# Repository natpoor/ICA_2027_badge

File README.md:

Arduino code and KiCAD files for the (v 0.2) ICA 2027 conference badge in Glasgow, Scotland.
The code works on the v 0.1 board (which is not posted here), the main change is the silkscreen but it should all work.
Most of the button-press (debouncing) and the sleep functions were (re)written by Claude Code (fall 2027 version).

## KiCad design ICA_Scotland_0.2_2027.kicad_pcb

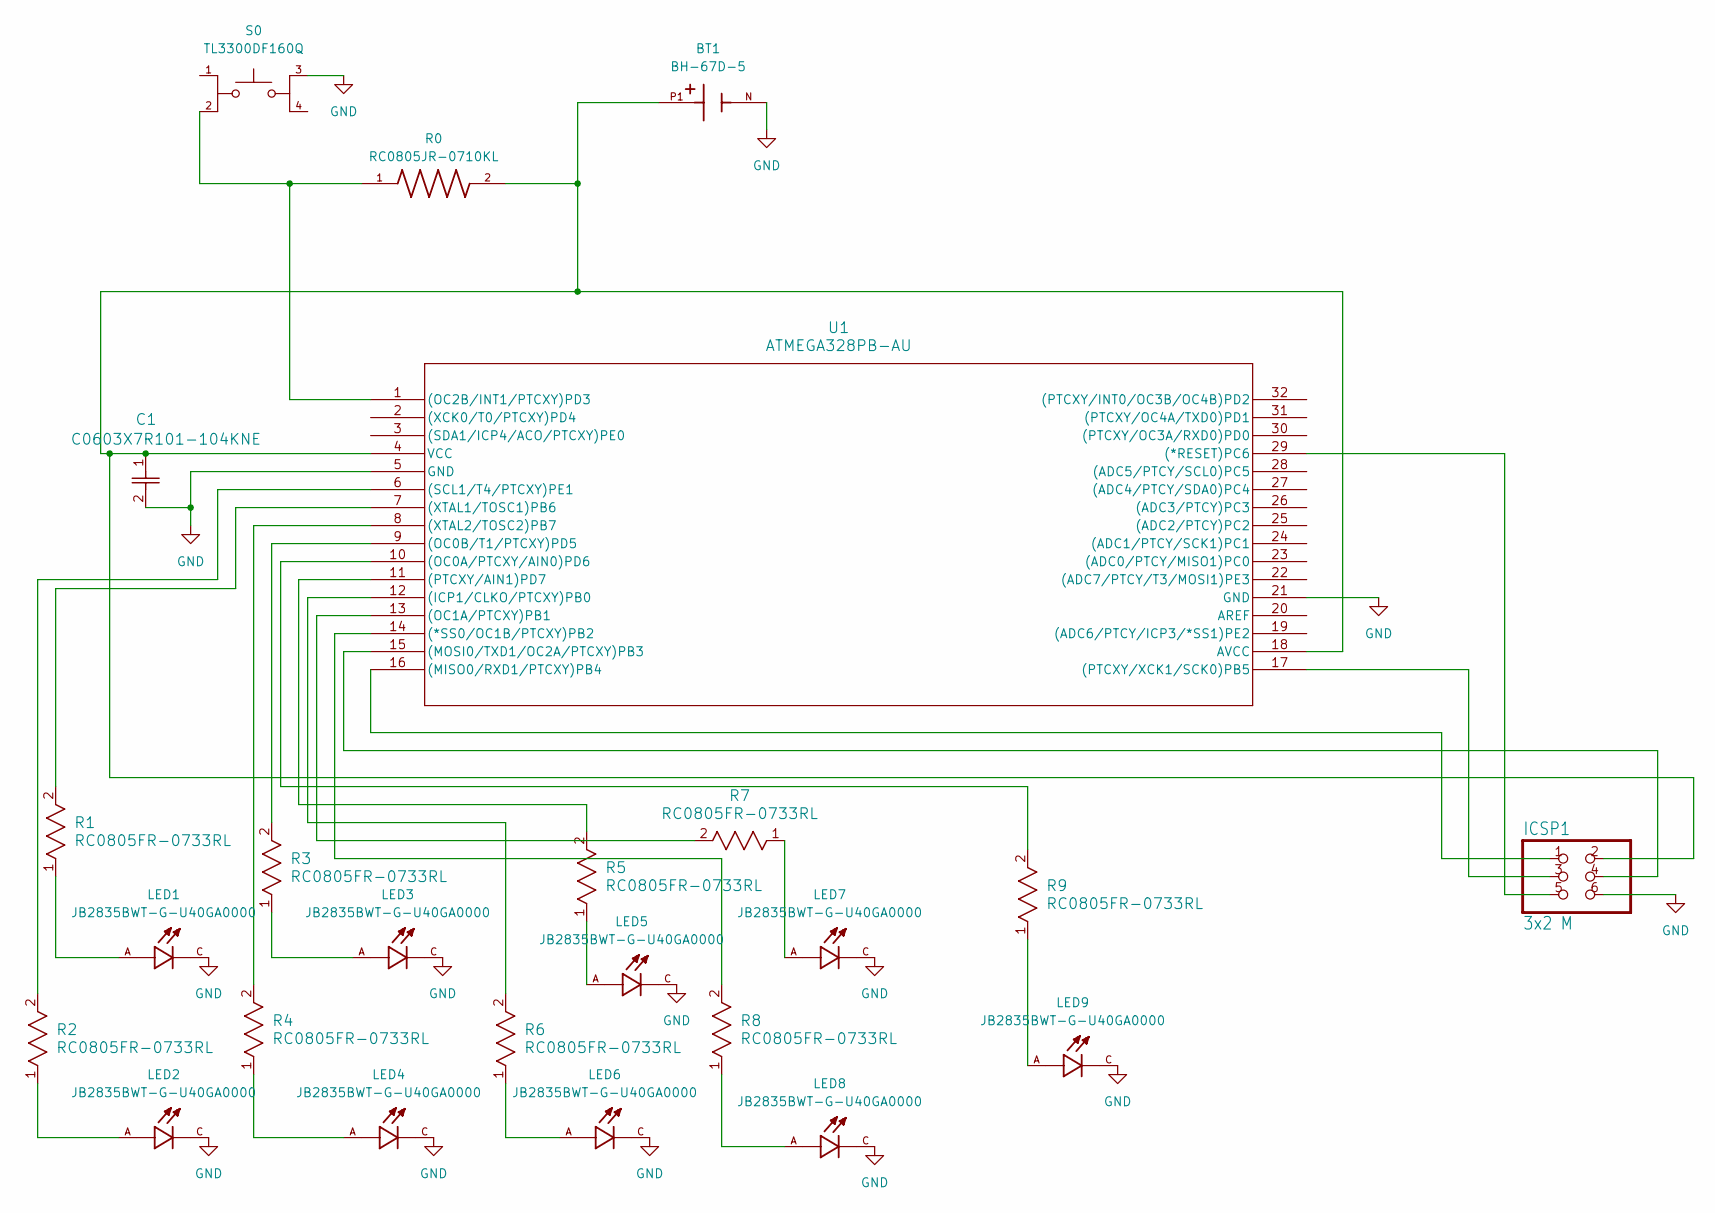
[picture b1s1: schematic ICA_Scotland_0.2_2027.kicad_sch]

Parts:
BT1: BH-67D-5; BAT_BH-67D-5; PARTREV A
C1: C0603X7R101-104KNE; CAP_C0603_VEN
ICSP1: 3x2 M; Conn_02x03_no_silk
LED1, LED2, LED3, LED4, LED5, LED6, LED7, LED8, LED9: JB2835BWT-G-U40GA0000; LED_JB2835BWT-G-U40GA0000-N0000001
R0: RC0805JR-0710KL; RESC2012X60N
R1, R2, R3, R4, R5, R6, R7, R8, R9: RC0805FR-0733RL; RC0805N_YAG
S0: TL3300DF160Q; SW_TL3300DF160Q; PARTREV A
U1: ATMEGA328PB-AU; 32A_MCH

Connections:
GND: BT1.N, C1.2, ICSP1.6, LED1.C, LED2.C, LED3.C, LED4.C, LED5.C, LED6.C, LED7.C, LED8.C, LED9.C, S0.3, U1.5 (GND), U1.21 (GND)
unnamed: LED1.A, R1.1
unnamed: LED2.A, R2.1
unnamed: LED3.A, R3.1
unnamed: LED4.A, R4.1
unnamed: LED5.A, R5.1
unnamed: LED6.A, R6.1
unnamed: LED7.A, R7.1
unnamed: LED8.A, R8.1
unnamed: LED9.A, R9.1
unnamed: ICSP1.5, U1.29 ((*RESET)PC6)
unnamed: R8.2, U1.14 ((*SS0/OC1B/PTCXY)PB2)
unnamed: R6.2, U1.12 ((ICP1/CLKO/PTCXY)PB0)
unnamed: ICSP1.1, U1.16 ((MISO0/RXD1/PTCXY)PB4)
unnamed: ICSP1.4, U1.15 ((MOSI0/TXD1/OC2A/PTCXY)PB3)
unnamed: R9.2, U1.10 ((OC0A/PTCXY/AIN0)PD6)
unnamed: R3.2, U1.9 ((OC0B/T1/PTCXY)PD5)
unnamed: R7.2, U1.13 ((OC1A/PTCXY)PB1)
unnamed: R0.1, S0.2, U1.1 ((OC2B/INT1/PTCXY)PD3)
unnamed: R5.2, U1.11 ((PTCXY/AIN1)PD7)
unnamed: ICSP1.3, U1.17 ((PTCXY/XCK1/SCK0)PB5)
unnamed: R2.2, U1.6 ((SCL1/T4/PTCXY)PE1)
unnamed: R1.2, U1.7 ((XTAL1/TOSC1)PB6)
unnamed: R4.2, U1.8 ((XTAL2/TOSC2)PB7)
unnamed: BT1.P1, C1.1, ICSP1.2, R0.2, U1.4 (VCC), U1.18 (AVCC)

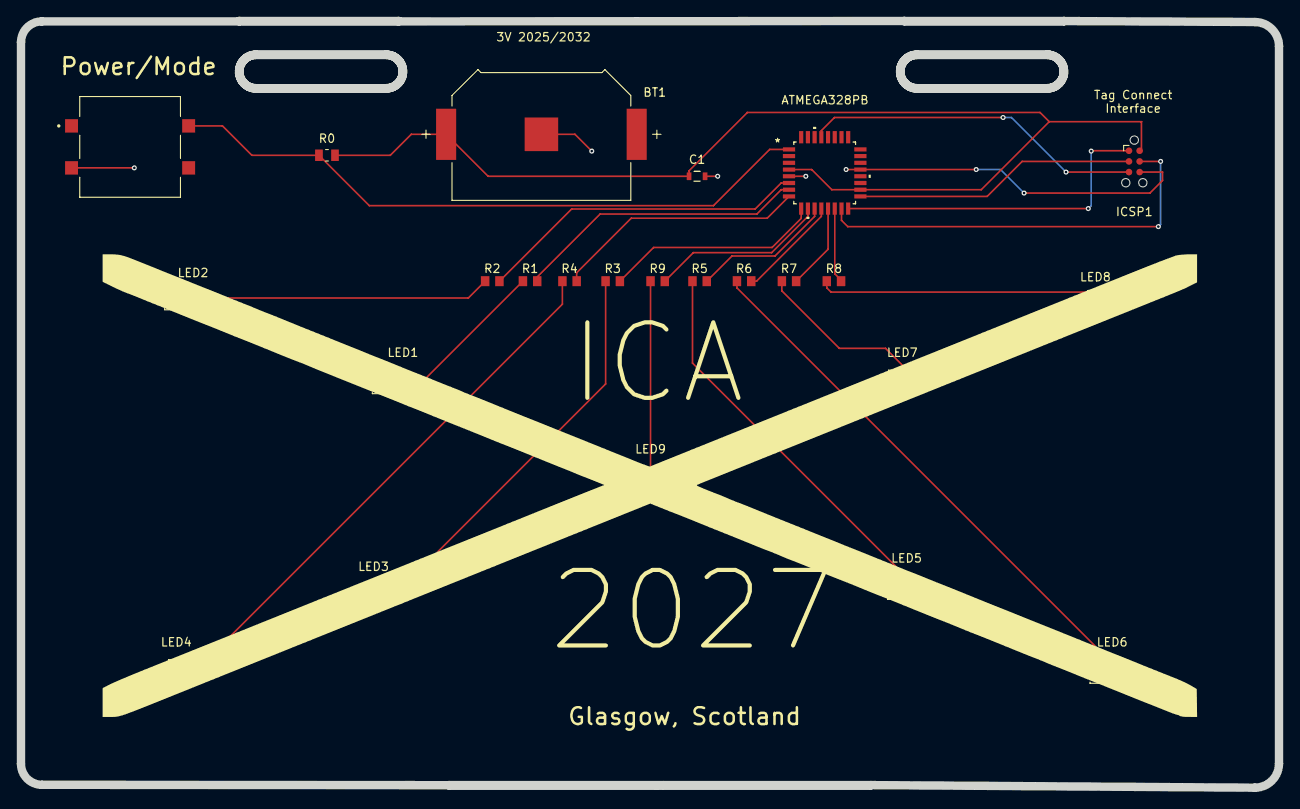
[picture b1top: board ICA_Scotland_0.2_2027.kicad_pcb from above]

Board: 2 copper layers, 149.9 x 91.3 mm, 24 parts (0 on the bottom side), 25 nets.

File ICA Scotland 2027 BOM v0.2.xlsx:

Item # | Designator | Component | Quantity | Manufacturer | MPN | Description | Mount Type | Notes | Notes 2 | Datasheet
1 | R1 - R9 | 33 Ohm Resistors for LEDs | 9 | YAGEO | RC0805FR-0733RL | RES 33 OHM 1% 1/8W 0805 | SMD | Specific manufacturer not important. |  | https://yageogroup.com/content/datasheet/asset/file/PYU-RC_G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
2 | LED1 - LED9 | White LEDs | 9 | Cree LED | JB2835BWT-G-U40GA0000-N0000001 | LED J NEUTRAL WHT 4000K 1411 | SMD | Specific manufacturer not important. |  | https://downloads.cree-led.com/files/ds/j/JSeries-2835-3V-Co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
3 | R0 | 10k Ohm resistor | 1 | YAGEO | RC0805JR-0710KL | RES 10K OHM 5% 1/8W 0805 | SMD | Specific manufacturer not important. |  | https://yageogroup.com/content/datasheet/asset/file/PYU-RC_G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
4 | S0 | Button | 1 | E-Switch | TL3300DF160Q | SWITCH TACTILE SPST-NO 0.05A 12V | SMD | Specific manufacturer not important. | Off-mom | https://configured-product-images.s3.amazonaws.com/Datasheet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
5 | U1 | ATMEGA 328PB | 1 | Microchip Technology | ATMEGA328PB-AU | IC MCU 8BIT 32KB FLASH 32TQFP | SMD | This is the important component (for programming). |  | https://ww1.microchip.com/downloads/en/DeviceDoc/40001907A.pdf
6 | C1 | Capacitor 0.1 µF | 1 | Murata Power Solutions Inc. | GCM21BR72A104KA37L | CAP CER 0.1UF 100V X7R 0805 | SMD | Specific manufacturer not important. |  | https://pim.murata.com/asset/pim4/ceramicCapacitorSMD/GCM21B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
7 | BT1 | Battery Holder | 1 | Adam Tech | BH-67D-5 | BATTERY RETAINER COIN 20MM SMD | SMD | Specific manufacturer not important. Please make sure the battery insertion sid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 |  | https://app.adam-tech.com/products/download/data_sheet/19697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
- | ICSP1 | Surface Pads | (1) | Tag Connect | (for the TC2030-IDC-NL) | Surface Pads and Holes (pads-only ICSP) | (DNP) | DNP | This is just the pads and holes on the PCB. No part to order. | https://www.tag-connect.com/wp-content/uploads/bsk-pdf-manag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
